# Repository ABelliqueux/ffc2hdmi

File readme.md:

# ffc2hdmi

**This is a WIP** ffc/csi to HDMI adapter base on the one found here : https://www.pcbway.com/project/shareproject/CSI_to_HDMI_Cable_Extension_Module.html  

You should be able to use this to connect a RPI camera module via a HDMI cable like so : RPI Csi camera connector > ffc2hdmi pcb > HDMI cable > ffc2hdmi pcb > Rpi camera CSI connector  

## Limitations

I have tested this PCB successfully with a RPI 4B+ and a raspicam V3.  
Currently, the **maximum length of the HDMI cable is 1.8M**. I tested with 3M and 10M cables and got timing error messages from libcamera.  
If you can test with other hardware and find that it works, please submit an issue stating your HW (rpi model, cam model and HDMI cable length.)  

The current length is enough for my usecase, but if you find a way to user longer cables, please open an issue stating your solution. I have spare PCBs and can do some tests (changing resistors/capacitors value ?).

## Parts needed 

 * This PCB x 2
 * 1.6Kohm resistor x 4
 * 100nf (0.1uf) ceramic capacitor x 2
 * FFC ([Molex 522711579](https://www.molex.com/en-us/products/part-detail/522711579)) connector x 2
 * HDMI [Molex 2086581201](https://www.molex.com/en-us/products/part-detail/2086581003) connector x 2
 * A HDMI cable (1.8M max)

## How do I get the PCB ?

You should be able to [grab the gerber files in this repo](https://github.com/ABelliqueux/ffc2hdmi/raw/refs/heads/main/ffc2hdmi_fab.zip) and use your favorite PCB maker like Jlcpcb or pcbway.

## Changelog

Changes are as follows:

 * Replace part with wrong pitch (0.5mm vs 1mm) [Hirose FH12-15S-0.5SH](https://www.hirose.com/product/p/CL0586-0523-6-55?lang=en) with [Molex 522711579](https://www.molex.com/en-us/products/part-detail/522711579)
 * Use through hole parts
 * Change HDMI footprint to fit [Molex 2086581201](https://www.molex.com/en-us/products/part-detail/2086581003)
 * Mounting holes are now 2.5mm instead of 2mm.

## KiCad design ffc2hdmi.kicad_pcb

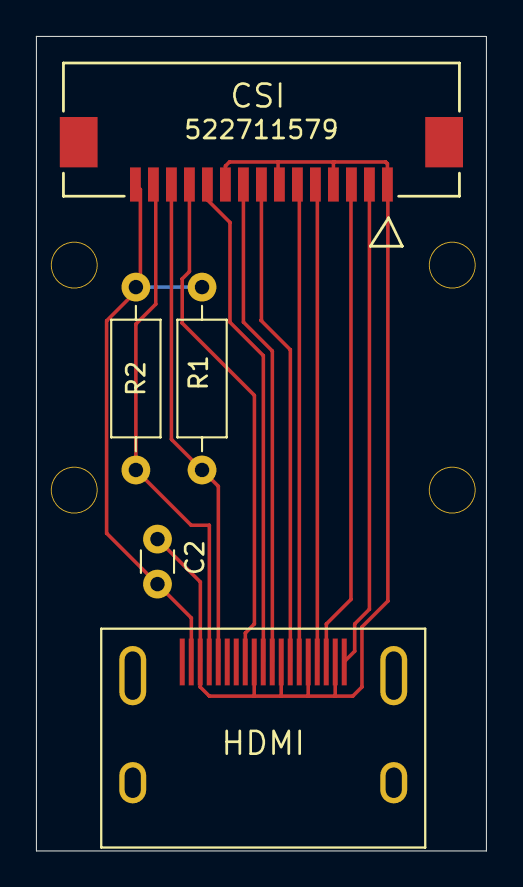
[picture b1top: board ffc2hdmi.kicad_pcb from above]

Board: 2 copper layers, 25.0 x 45.2 mm, 9 parts (0 on the bottom side), 12 nets.

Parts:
@HOLE0, @HOLE1, @HOLE2, @HOLE3: (no value)
C2: 0.1uF; C_Disc_D3.0mm_W1.6mm_P2.50mm
HDMI: HDMI Molex 2086581081; HDMI
R1, R2: 1,6K; R_Axial_DIN0207_L6.3mm_D2.5mm_P10.16mm_Horizontal
X1: CON_522711579_MOL

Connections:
+3V3: C2.1, HDMI.P$2 (+5V), R1.2, R2.2, X1.15 (1)
/CAM1-DN0: HDMI.P$19 (TMDS_DATA2+), X1.2 (1)
/CAM1-DN1: HDMI.P$16 (DATA1+), X1.5 (1)
/CAM1-DP0: HDMI.P$17 (TMDS_DATA2-), X1.3 (1)
/CAM1-DP1: HDMI.P$14 (DATA1-), X1.6 (1)
/CAM1_CN: HDMI.P$13 (DATA0+), X1.8 (1)
/CAM1_CP: HDMI.P$11 (DATA0-), X1.9 (1)
/CAM_CLK: HDMI.P$8 (TMDS_CLOCK-), X1.12 (1)
/CAM_GPIO: HDMI.P$10 (TMDS_CLOCK+), X1.11 (1)
/SCL0: HDMI.P$5 (SCL(I2C_DDC)), R1.1, X1.13 (1)
/SDA0: HDMI.P$4 (SDA(I2C_DDC)), R2.1, X1.14 (1)
GND: C2.2, HDMI.P$3 (GND), HDMI.P$9 (TMDS_CLOCK_SHIELD), HDMI.P$12 (DATA0_SHIELD), HDMI.P$15 (DATA1_SHIELD), HDMI.P$18 (TMDS_DATA2_SHIELD), X1.1, X1.4 (1), X1.7 (1), X1.10 (1)

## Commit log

2024-12-17 Update parts listing
2024-12-19 Add sch to readme
2025-01-03 PCB is working, add infos, pic
